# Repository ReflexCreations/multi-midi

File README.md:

# Multi-MIDI

Multi-MIDI is a 1-to-8 or more MIDI thru box. This is definitely not a novel idea, but it's mainly for fun and to keep it cheap. Everything here was made with open source software and with the publicly available MIDI specifications.

All the files are available, so you can make your own. In brief, what you'll need to get the full thing:

- Have the circuit board manufactured; we usually used JLCPCB for this, who also can do assembly of the surface-mount components
- Get all the components; if you went with assembly by JLCPCB, you only need to get the DIN-5 connectors, barrel jack, and 3-pin header. A full bill of materials is below.
- Get the 3D printed case; either if you have access to a 3D printer, or get some online service to make it for you
- 4 heat-sinkable threaded inserts
- 4 10mm long M3 screws
- Soldering iron
- Screwdriver
- 5V power supply with centre positive barrel connector (2.1mm pin, 5.5mm diameter)

## Photos

The tab shown above is for mounting, for example, to the back of a cabinet.

Heat-set threaded inserts go into the bottom part of the case's screwholes, allowing the use of M3 machine screws to assemble the box.

Exploded view of the case and circuit board, in FreeCAD

## How to make one

The least-work way is to order the Printed Circuit board (PCB) assembled from JLCPCB. You can also order a bare board from any PCB prototyping place, and then source and solder all the components yourself. 

### Board: The JLCPCB assembled route

#### 1. Grab the latest PCB manufacturing files

1. Go to the [Latest release](https://github.com/ReflexCreations/multi-midi/releases) and download the .zip file ending in `.gerber.zip`. This contains all the PCB fabrication outputs from KiCAD. Alternatively, clone or download this repository, open the project from the pcb/multi-midi folder in KiCad and [export the gerber files yourself](https://support.jlcpcb.com/article/44-how-to-export-kicad-pcb-to-gerber-files).

2. Download the BOM file, ending in `.jlc.bom.csv`. This contains a list of all the parts that JLCPCB will supply and install themselves.

3. Download the "centroid" position file, ending in `.jlc.top-pos.csv`. This contains the positions and orientations for the parts JLCPCB will assemble.

If you want, you can generate the latter two files yourself, but this is trickier than generating the gerber files since  a 3rd party script needs to be installed, and output files manually edited to work with JLCPCB. Documentation: [How to generate the BOM and Centroid file from KiCAD](https://support.jlcpcb.com/article/84-how-to-generate-the-bom-and-centroid-file-from-kicad)

#### 2. Place the order with JLCPCB

1. Go to [JLC's ordering page](https://cart.jlcpcb.com/quote)
2. Click "Add your gerber file", select the `.gerber.zip` file from above
3. Pick a board color or leave it at the default green. Last time I checked different colors only affect build time, not price.
4. Pick a surface finish or leave it on the default. The default is cheapest, but contains lead. ENIG gives the pads a nice golden finish instead of silver.
5. For "Remove Order Number", pick "Specify a location"; this means they'll print the order number where the board design says "JLCJLCJLCJLC" (on the underside of the board) instead of a spot you don't control.
6. Leave all the other options as they are.
7. Scroll down to "SMT Assembly" and switch it on
8. Select "assemble top side"
9. Pick a quantity; if you only want one, 2 will be the minimum here
10. Click "Confirm".
11. On the right side of the page, click "Next"
12. Click "Add BOM File"; upload the `.jlc.bom.csv` file
13. Click "Add CPL File"; upload the the `.jlc.top-pos.csv` file from earlier
14. Click "Next"
15. Review the specified parts; they should all be "confirmed" in the right column, so you can leave everything as it is.
16. Click "Next"
17. In the preview, some ICs might look like they're oriented wrong. This is a problem with their viewer; the files are correct. If it ends up wrong (not aligning with the pads), they'll either correct it or email you to find a solution.
18. Click "Save to cart"
19. Click "Check out Securely"
20. Add your shipping and billing details
21. Select a shipping method. Usually the DHL-based ones are fine. You can gamble on whether or not you want duty and customs paid up front (more expensive), or hope for the best with the cheaper option, in which case you might get a bill from the courier later.
22. Click "Continue" when you're happy
23. Click "submit order"
24. Do what you need to do for payment
25. Wait for your boards to get delivered

#### 3. Order the remaining through-hole parts

The remaining parts are as follows:

- 9x DIN-5 connector: `Deltron 671-0501` or equivalent. Some possible sources:
    - [Farnell UK](https://uk.farnell.com/deltron-components/671-0501/din-audio-video-conn-jack-5pos/dp/2989966)
    - [RS Components UK](https://uk.rs-online.com/web/p/din-connectors/1806737/)
    - [Technobots](https://www.technobotsonline.com/5-pin-180-deg-din-pcb-socket.html)
- 1x Barrel jack: `Wurth Elektronik 694106301002` Some possible sources:
    - [Farnell UK](https://uk.farnell.com/wurth-elektronik/694106301002/connector-power-entry-jack-3a/dp/2472149?ost=694106301002)
    - [RS Components UK](https://uk.rs-online.com/web/p/dc-power-connectors/1224879/)
- Generic 2.54mm pitch single row pin header - you can find this in any electronics store, eBay, or Amazon. You can get any number of them and use pliers to break 3 pins off.
- Generic 2.54mm pitch jumper; a piece that connects two pins together. You can get these from many places too, but here are some sources:
    - [RS Components UK](https://uk.rs-online.com/web/p/jumpers-shunts/2518503/)
    - [Farnell UK](https://uk.farnell.com/harwin/m7581-05/jumper-socket-2pos-pin-header/dp/2396303)

If you plan to connect more than one board together, you'll also want some connectors for the right hand side:

- 2x JST PH 4 way Right angle connector:` JST S4B-PH-K-S(LF)(SN)` Possible sources:
    - [RS Components UK](https://uk.rs-online.com/web/p/pcb-headers/8201507/)   
    - [Farnell UK](https://uk.farnell.com/jst-japan-solderless-terminals/s4b-ph-k-s-lf-sn/header-tht-right-angle-2mm-4way/dp/9492488?ost=s4b-ph-k-s%28lf%29%28sn%29)

- 8x JST PH Crimp contact `JST BPH-002T-P0.5S` Possible sources:
    - [RS Components UK](https://uk.rs-online.com/web/p/crimp-contacts/8201456/)
    - [Farnell UK](https://uk.farnell.com/jst-japan-solderless-terminals/bph-002t-p0-5s/contact-loose-piece-0-05-0-22mm/dp/3617210?ost=bph-002t-p0.5s)

- Wire (24 AWG thickness), enough for 4 lengths of however long you want the connecting cable to be - can be found on eBay, Amazon, various electric supplies stores

- A crimping tool like `Fdit SN-28B`

Alternatively, find some pre-crimped cables, possibly on aliexpress; then you don't need the crimp contacts, wire, and crimping tool.

#### 4. Solder the remaining parts onto the board

Fairly evident where each of them go, though a more detailed guide here could be helpful. Pull requests welcome. :-)

If you're not planning to expand the board with another, you can leave out the JST connectors. In stead of the 3 pin header + jumper, you can use a spare piece of wire or component lead cutoff,
and connect the bottom two holes for the pin header connector that way.

#### 5. Connect a jumper in "INT" mode

On the pin header in the middle of the board, push a jumper down over the bottom two pins, as demonstrated on the board, for "INT" mode.

#### 5. Get a Power supply

To power this thing you need a power supply that outputs 5V. The rated current is pretty irrelevant as this circuit will not draw more than 100 milliamps. To be compatible with the barrel jack on the board, it needs a barrel connector with a pin size of 2.1mm (2mm works too) and outer diameter of 5mm. It needs to be center positive. Generally can be found on eBay or Amazon or any number of places. One of those with switchable connectors can also work. A USB charger + a USB->barrel connector cable would also work just fine.

### Case: 3D printing

1. Download the .stl files from the latest release (where you found the PCB manufacturing file). There are two of them, one for the top portion of the box, and one for the bottom.
2. If you have a 3D printer yourself, use your favorite slicing software (like Cura or Slic3r) to generate the .gcode files appropriate for your printer, and start the print job. Note that you may have to turn the top part upside down so the flat side faces the printer surface. If you don't have a 3D printer, either ask a nearby maker/hackerspace or a friend for help, or find an online service that will send you the printed parts. An online [search for "3D printing service"](https://duckduckgo.com/?q=3d+printing+service) should get you what you need.
3. Get some M3 heat-set threaded inserts. The ones in the pictures are about 6mm tall. You can find various ones on Amazon and eBay; it mostly matters that they're M3.
4. Using small pliers and a soldering iron set to ~200 degrees Celcius, gently insert them into the holes on the bottom part of the case

#### Final assembly

1. Put the finished circuit board on the bottom portion of the case (where you've just installed the inserts)
2. Put the top side on, fitting it in the bottom. This may take a little bit of pushing as it's a fairly tight fit.
3. Insert 10mm long M3 screws into the screwholes on the top and tighten them
4. All done.

---

## Usage

Let's first define a few terms:

- MIDI source: The device you are sending MIDI data from. This could be a MIDI keyboard, or a MIDI interface connected to your computer.
- Multi-MIDI: The device this page is all about
- Multi-MIDI input: The MIDI connector on the short side of the Multi-MIDI
- Multi-MIDI output: any one of the 8 other MIDI outputs on either long side of the Multi-MIDI
- Instrument: A device you want to send MIDI data to, such as a synthesizer, digital piano, drum machine... as long as it has a "MIDI in" port.

With that out of the way, here's how you use the Multi-MIDI:

1. Connect your MIDI source's "MIDI out" port to the Multi-MIDI input with a DIN-5 MIDI Cable
2. For each of your instruments connect its MIDI in port to one of the Multi-MIDI outputs
3. Connect the power supply to the Multi-MIDI.
4. Consult the manual of each of your instruments to configure which MIDI channel it should listen to. This is a number from 1 to 16.
5. On your MIDI source, assign the same channel numbers to the tracks/channels/... so they correspond to the right instrument
6. Now you can use all those instruments from one MIDI source.

### Chaining two boards

If you have two of these boards, you can connect them together in 2 possible configurations:

1. Expander: This effectively turns the combination into one 1-to-16 MIDI thru box
2. Power supply sharing: The devices work independently, so there are 2x 1 to 8 expanders, but only one power supply needs to be connected.

Let's define "board 1" as the first board where you've got MIDI input and the power supply connected.

"Board 2" will be the one we're connecting up to board 1 to expand its functionality.

#### A note on the case

Note that at this time, there is only a case design for a single board. If you decide to stack more than one board to create an expanded device,
you may want to adapt the case design to be larger, to accomodate both. There is a clearing provided in the PCB design to allow connecting cables
between the boards internal to a box, for this purpose.

#### Expander mode:

1. On board 1, connect the jumper in "INT" mode. This will make it use its own MIDI in port as the source of MIDI data.
2. On board 2, connect the jumper in "EXT" mode. This will make it use MIDI input coming through the 4-pin JST connector.
3. Connect a cable between board 1's "Expansion output" connector and board 2's "Expansion input" connector
4. Connect your MIDI source's "MIDI out" port to board 1's MIDI input
5. Connect each of your instruments: connect their MIDI in ports to one of board 1's or board 2's MIDI outputs.
6. Connect the power supply to board 1's power input

#### Power supply sharing mode:

1. On both board 1 and board 2, connect the jumper in "INT" mode. This will make both of them use their respective MIDI input ports
2. Connect a cable between board 1's "Expansion output" connector and board 2's "Expansion input" connector
3. Connect your first MIDI source's "MIDI out" to board 1's MIDI input
4. Connect your second MIDI source's "MIDI out" to board 2's MIDI input
5. Connect each of your instruments: connect their MIDI in ports to one of board 1's or board 2's MIDI outputs, choosing between the boards
   depending on which source you wish to connect to
6. Connect the power supply to board 1's power input

---

## Troubleshooting

At this time, it's unknown what common issues might occur in this process. If you're having any issues, please open an issue on GitHub and we can help resolve it / potentially improve documentation.

---

## Full Bill of Materials for one circuit board

A CSV file for this table is also available in the release downloads.

| Quantity | Reference  | Value              | Footprint                             | LCSC Component No. | Mfr. Part No.          |
|----------|------------|--------------------|---------------------------------------|--------------------|------------------------|
| 4        | C1 – C4    | 100n               | 0603 / 1608Metric                     | C14663             |                        |
| 2        | C5 - C6    | 47u                | 1206 / 3216 Metric                    | C96123             |                        |
| 1        | D1         | 1N4148W            | SOD-123                               | C81598             |                        |
| 2        | J10 - J11  | Conn_01x04_Male    | JST_EH_S4B-EH_1x04_P2.50mm_Horizontal |                    | JST S4B-PH-K-S(LF)(SN) |
| 1        | J12        | Barrel_Jack_Switch | BarrelJack_Wuerth_6941xx301002        |                    | Wurth 694106301002     |
| 1        | J13        | Conn_01x03_Male    | PinHeader_1x03_P2.54mm_Vertical       |                    |                        |
| 9        | J1 – J9    | DIN-5_180degree    | Custom: Deltron 671-0501              |                    | Deltron 671-0501       |
| 18       | L1 - L18   | SDFL2012S100KTF    | 0805 / 2012 Metric                    | C1046              |                        |
| 17       | R1 – R17   | 220                | 0603 / 1608 Metric                    | C22962             |                        |
| 1        | R26        | 10k                | 0603 / 1608 Metric                    | C25804             |                        |
| 2        | U1 – U2    | LM358              | SOIC-8_3.9x4.9mm_P1.27mm              | C7950              |                        |
| 1        | U3         | 6N137              | SSO-8_6.7x9.8mm_P2.54mm_Clearance8mm  | C110020            |                        |

---

## Theory of operation

As per the MIDI electrical spec, a MIDI input should be driven through an opto-isolator. In this case that's the `6N137`. The MIDI input signal
drives just the LED in the opto-isolator, so it is completely electrically isolated from the rest of the circuit.

`D1` is a protection diode, connected the opposite way compared to the opto-isolator's diode. This provides a short-circuit path in case the incoming MIDI is polarised the wrong way,
ensuring the opto-isolator doesn't get reverse-biased, and potentially broken.

The output of the opto-isolator is connected to opamps (LM358) set up in a voltage follower configuration. These act as buffers for the signal, able to drive a bit more current than
the opto-isolator can supply. The circuit is set up to supply the signal for 2 outputs per voltage follower; so for all 8, 4 opamps are needed.

Further, there are 220 ohm resistors to limit the current through the opto-isolator diode on the receiving end, as well as small inductors which are meant to filter out high frequency
noise, such as from low quality power supplies.

A jumper in the middle of the board selects which source of MIDI should be buffered out to the output ports. Either "INT" (MIDI coming in from the on-board MIDI in port through the opto-isolator,
or "EXT", coming in through the "Expansion input" connector. Not connecting a jumper to either will result in no MIDI making it to the output ports.

---

## Credits

- The 3D model of the barrel jack used on the PCB design was made by [DL2DW - Dirk Wouters](https://grabcad.com/dl2dw.dirk.wouters-1) and can be found here: [Power Barrel Connector Jack on GRABCAD](https://grabcad.com/library/power-barrel-connector-jack-1)
- The circuitry for single MIDI thru is taken almost directly from the [MIDI DIN electrical specification](https://www.midi.org/specifications/item/midi-din-electrical-specification).
- [KiCad](https://kicad.org/) was used for the electronics design (schematic, circuit board)
- [FreeCAD](https://www.freecadweb.org/) was used to model the case, as well as the 3D representation of the DIN-5 connectors used in the 3D render of the PCB.

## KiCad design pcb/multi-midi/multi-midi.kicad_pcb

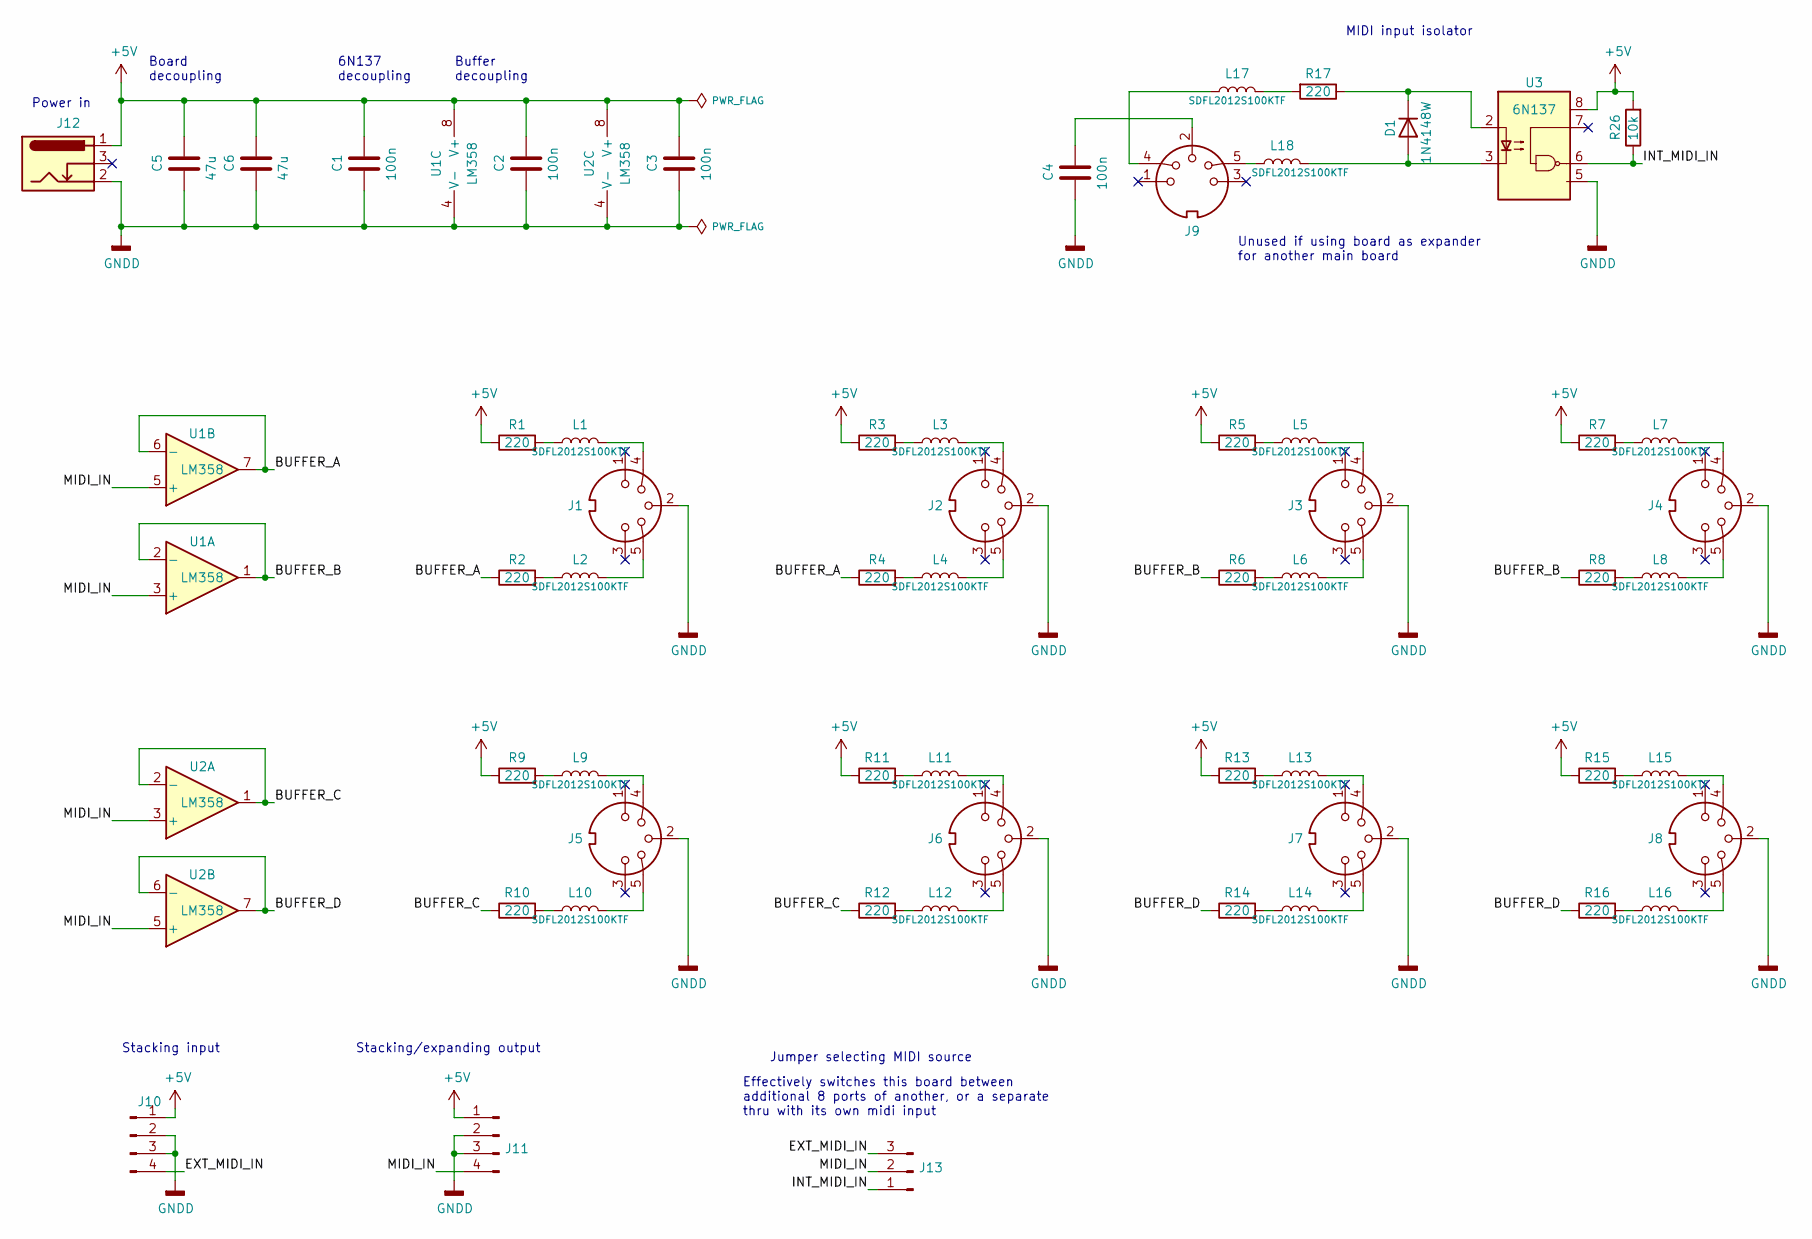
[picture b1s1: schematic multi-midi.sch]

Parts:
C1, C2, C3, C4: 100n; C_0603_1608Metric; LCSC C14663
C5, C6: 47u; C_1206_3216Metric; LCSC C96123
D1: 1N4148W; D_SOD-123; LCSC C81598
J1, J2, J3, J4, J5, J6, J7, J8, J9: DIN-5_180degree; DIN-5
J10, J11: Conn_01x04_Male; JST_EH_S4B-EH_1x04_P2.50mm_Horizontal
J12: Barrel_Jack_Switch; BarrelJack_Wuerth_6941xx301002
J13: Conn_01x03_Male; PinHeader_1x03_P2.54mm_Vertical
L1, L2, L3, L4, L5, L6, L7, L8, L9, L10, L11, L12, L13, L14, L15, L16, L17, L18: SDFL2012S100KTF; L_0805_2012Metric; LCSC C1046
R1, R2, R3, R4, R5, R6, R7, R8, R9, R10, R11, R12, R13, R14, R15, R16, R17: 220; R_0603_1608Metric; LCSC C22962
R26: 10k; R_0603_1608Metric; LCSC C25804
U1, U2: LM358; SOIC-8_3.9x4.9mm_P1.27mm; LCSC C7950
U3: 6N137; SSO-8_6.7x9.8mm_P2.54mm_Clearance8mm; LCSC C110020

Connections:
+5V: C1.1, C2.1, C3.1, C5.1, C6.1, J10.1, J11.1, J12.1, R1.1, R3.1, R5.1, R7.1, R9.1, R11.1, R13.1, R15.1, R26.2, U1.8 (V+), U2.8 (V+), U3.8 (VCC)
/BUFFER_A: R2.1, R4.1, U1.6 (-), U1.7
/BUFFER_B: R6.1, R8.1, U1.1, U1.2 (-)
/BUFFER_C: R10.1, R12.1, U2.1, U2.2 (-)
/BUFFER_D: R14.1, R16.1, U2.6 (-), U2.7
/EXT_MIDI_IN: J10.4, J13.3
/INT_MIDI_IN: J13.1, R26.1, U3.6 (VO2)
/MIDI_IN: J11.4, J13.2, U1.3 (+), U1.5 (+), U2.3 (+), U2.5 (+)
GNDD: C1.2, C2.2, C3.2, C4.2, C5.2, C6.2, J1.2, J2.2, J3.2, J4.2, J5.2, J6.2, J7.2, J8.2, J10.2, J10.3, J11.2, J11.3, J12.2, U1.4 (V-), U2.4 (V-), U3.5 (GND)
unnamed: C4.1, J9.2
unnamed: D1.1 (K), R17.1, U3.2 (C1)
unnamed: D1.2 (A), L18.2, U3.3 (C2)
unnamed: J1.4, L1.2
unnamed: J1.5, L2.2
unnamed: J2.4, L3.2
unnamed: J2.5, L4.2
unnamed: J3.4, L5.2
unnamed: J3.5, L6.2
unnamed: J4.4, L7.2
unnamed: J4.5, L8.2
unnamed: J5.4, L9.2
unnamed: J5.5, L10.2
unnamed: J6.4, L11.2
unnamed: J6.5, L12.2
unnamed: J7.4, L13.2
unnamed: J7.5, L14.2
unnamed: J8.4, L15.2
unnamed: J8.5, L16.2
unnamed: J9.4, L17.1
unnamed: J9.5, L18.1
unnamed: L1.1, R1.2
unnamed: L2.1, R2.2
unnamed: L3.1, R3.2
unnamed: L4.1, R4.2
unnamed: L5.1, R5.2
unnamed: L6.1, R6.2
unnamed: L7.1, R7.2
unnamed: L8.1, R8.2
unnamed: L9.1, R9.2
unnamed: L10.1, R10.2
unnamed: L11.1, R11.2
unnamed: L12.1, R12.2
unnamed: L13.1, R13.2
unnamed: L14.1, R14.2
unnamed: L15.1, R15.2
unnamed: L16.1, R16.2
unnamed: L17.2, R17.2

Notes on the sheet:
MIDI input isolator
Power in
6N137 decoupling
Buffer decoupling
Board decoupling
Stacking input
Stacking/expanding output
Jumper selecting MIDI source
Effectively switches this board between additional 8 ports of another, or a separate thru with its own midi input
Unused if using board as expander for another main board

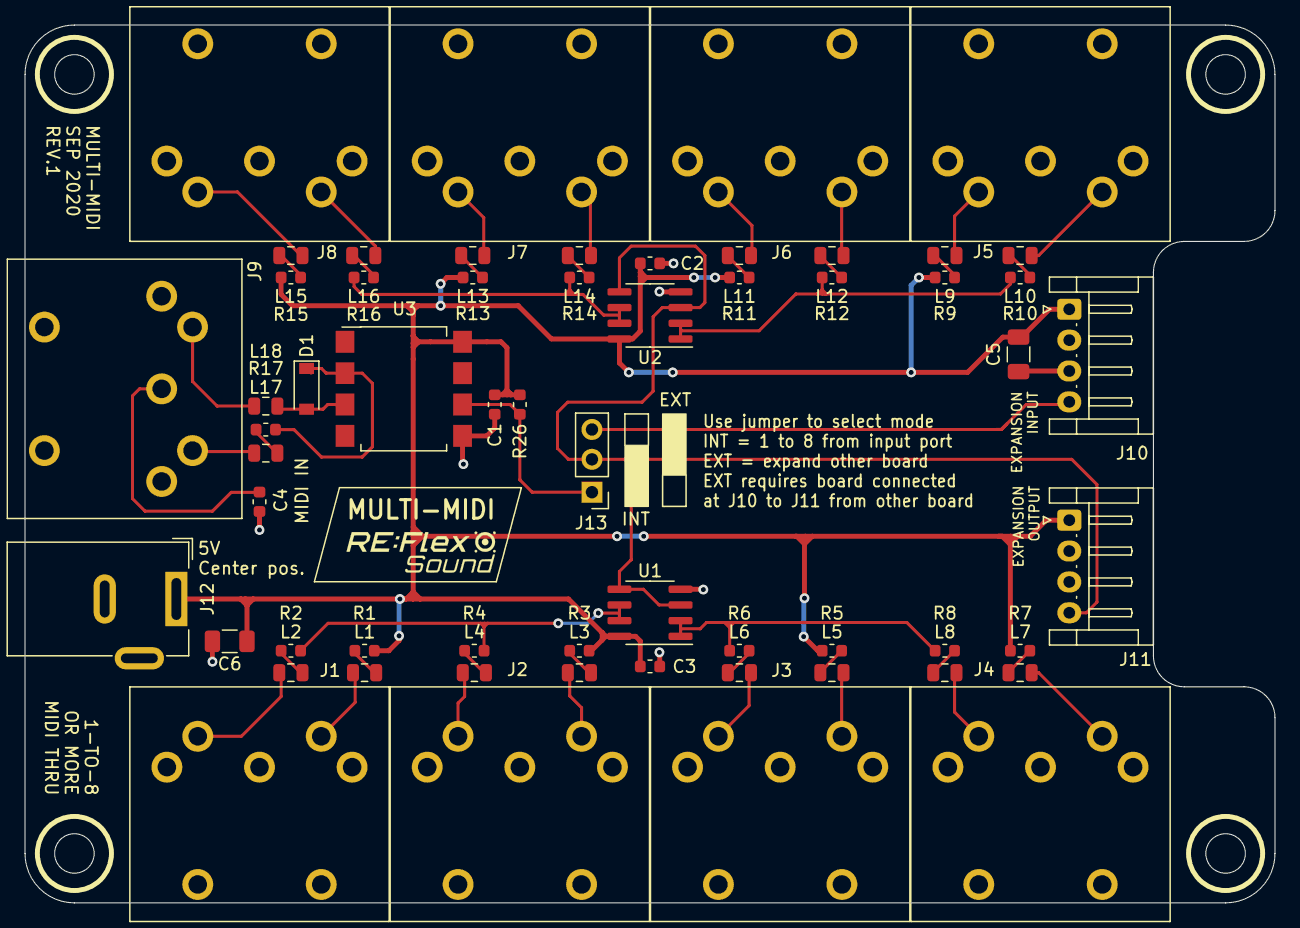
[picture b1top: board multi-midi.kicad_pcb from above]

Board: 2 copper layers, 101.2 x 71.1 mm, 59 parts (0 on the bottom side), 47 nets.

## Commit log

2019-05-06 Initial commit: readme, license
2019-05-09 Sketch schematic diagram in kicad
    Nothing tested in real life yet. 6n137 circuitry based on old MIDI input
    module.
2020-09-12 Actually do this. Redrew schematic, design PCB
2020-09-12 Add gitignore
2020-09-12 Swap out inductors with a "basic part"
    Version of how I ordered rev0.
2020-09-29 Add FreeCAD backup files to gitignore
2020-09-29 Add FreeCAD design for a 3D-printable case
2020-09-29 Create 3D model for DIN-5 connector
    There probably exist some that are close enough online, but this was a
    fun exercise anyway. Got some pointless detail in there, but I learned
    things, hurray!
2020-09-29 Add barrel jack 3D Model (from internet)
    Found on GrabCad: https://grabcad.com/library/power-barrel-connector-jack-1
    To return the favour, I've published the DIN-5 connector added in the
    previous commit to GrabCad too.
2020-09-29 Update PCB with newly added 3D models
2020-09-29 Add an export of the board 3D model in STEP format
2020-09-29 Rejigger case design to include the PCB model
    Also stuck the existing bits into components and put them all together
2020-09-29 Add PNG images of case, assembled and exploded
2020-09-29 Add case top and bottom STLs for 3D printing
2020-09-29 Crop case PNG images a bit
2020-09-29 Add some photos for documentation
2020-09-30 Fix board-level caps value, part No.; update to rev1
2020-09-30 Describe ordering and build process in readme
    The image links are broken because this repo isn't public yet at the moment.
    Also describes usagage, theory of operation, lists a BOM, credits.
2020-09-30 Fix a typo in the README: boad->board
2020-09-30 Update name, year in LICENSE
2020-09-30 Fix several typos in README
    With thanks to https://github.com/loansindi for the proofread.
2021-11-08 Update README.md
    https://forum.kicad.info/t/warning-avoid-all-links-to-kicad-pcb-org-use-kicad-org/31521
